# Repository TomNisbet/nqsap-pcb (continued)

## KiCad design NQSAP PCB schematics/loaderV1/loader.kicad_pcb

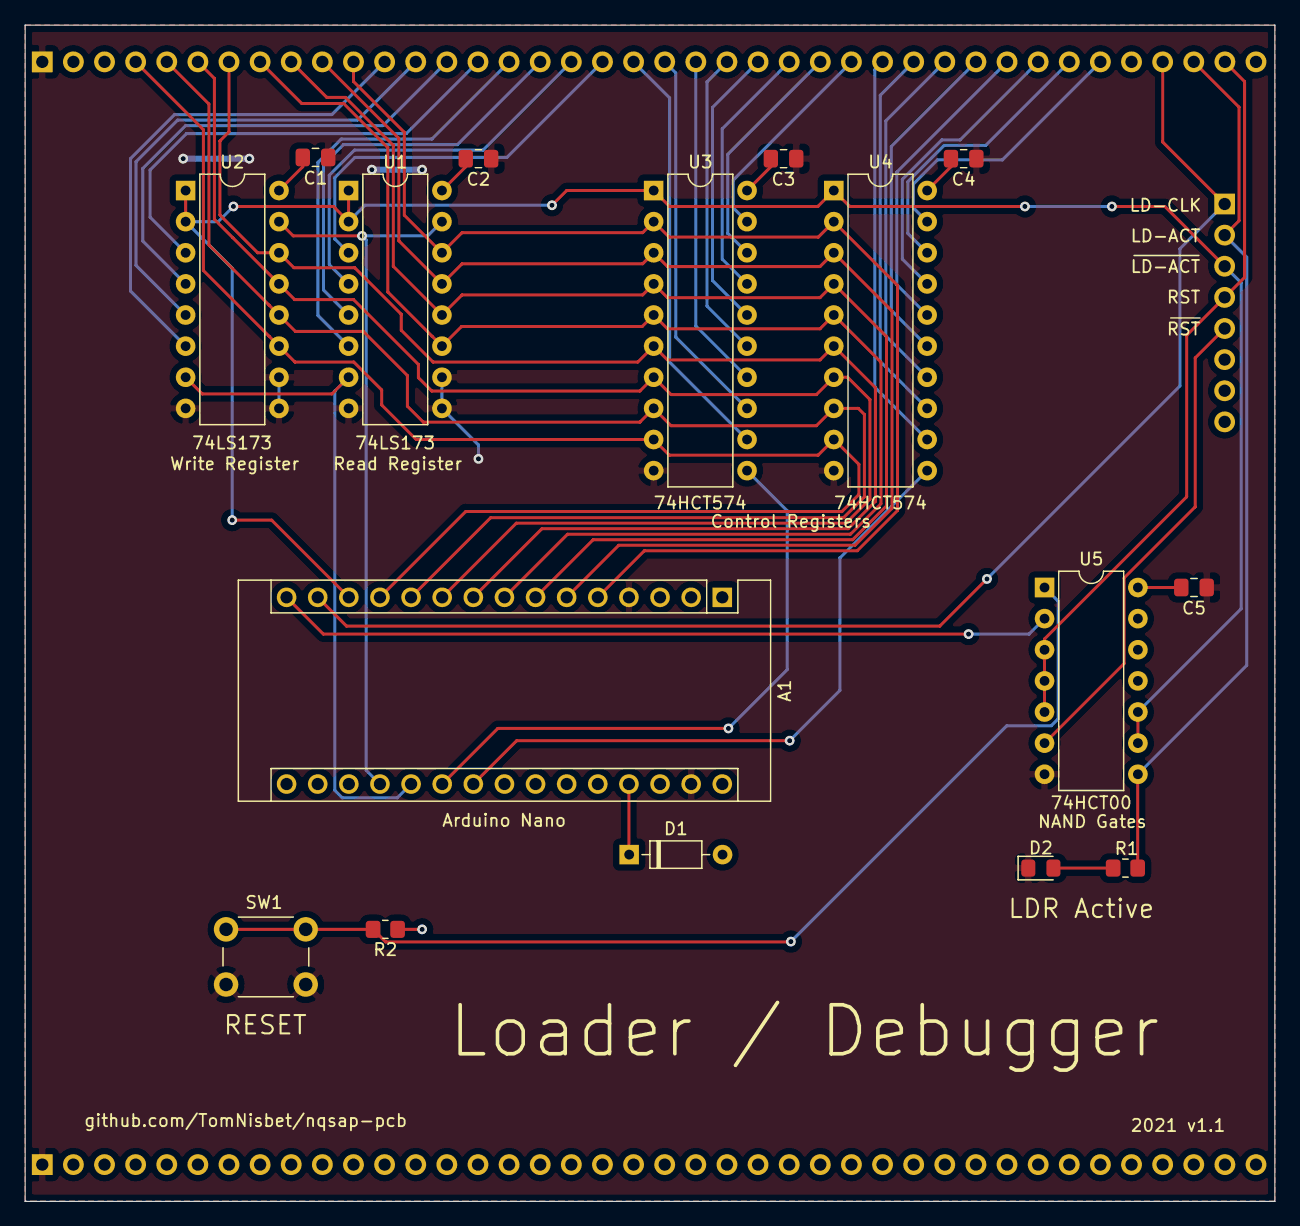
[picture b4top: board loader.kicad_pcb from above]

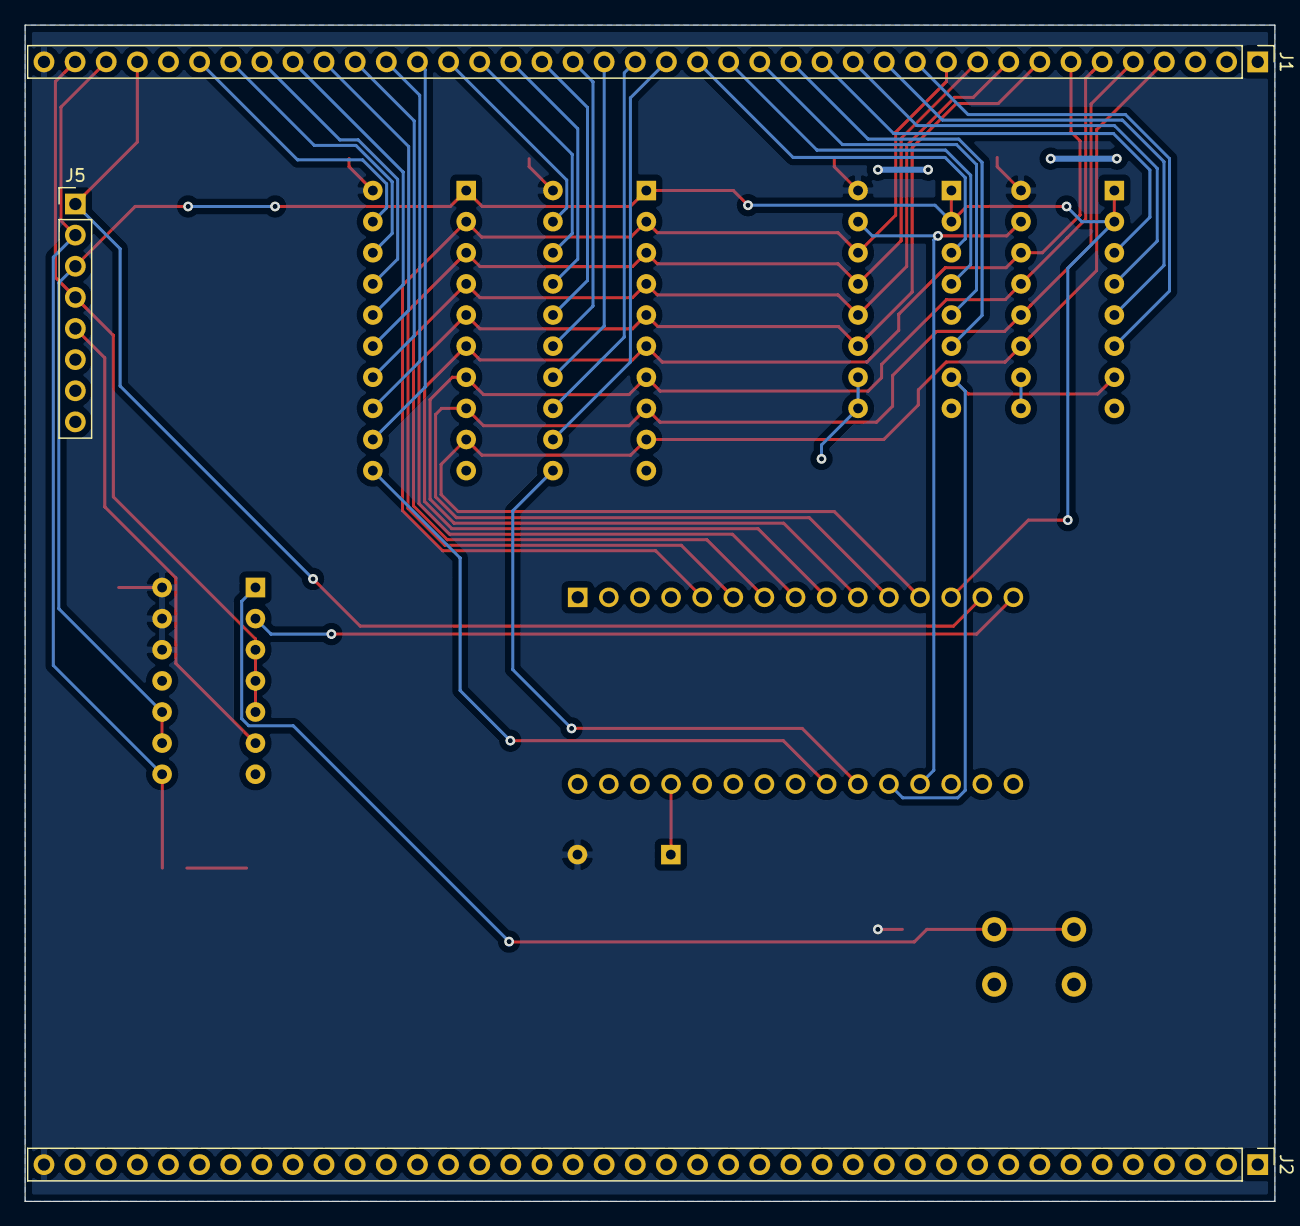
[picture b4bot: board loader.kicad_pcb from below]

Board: 2 copper layers, 102.0 x 96.0 mm, 19 parts (3 on the bottom side), 47 nets.

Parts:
A1: Arduino Nano; Arduino_Nano
C1, C2, C3, C4, C5: 0.1uF; C_0805_2012Metric_Pad1.18x1.45mm_HandSolder
D1: diode; D_DO-35_SOD27_P7.62mm_Horizontal
D2: LDR Active; LED_0805_2012Metric_Pad1.15x1.40mm_HandSolder
J1, J2: Bus; PinHeader_1x40_P2.54mm_Vertical
J5: Conn_02x08; PinHeader_1x08_P2.54mm_Vertical
R1: 100; R_0805_2012Metric_Pad1.20x1.40mm_HandSolder
R2: 10K; R_0805_2012Metric_Pad1.20x1.40mm_HandSolder
SW1: RESET; SW_PUSH_6mm_H7.3mm
U1, U2: 74LS173; DIP-16_W7.62mm
U3, U4: 74HCT574; DIP-20_W7.62mm
U5: 74HCT00; DIP-14_W7.62mm

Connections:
+5V: C1.2, C2.2, C3.2, C4.2, C5.2, D1.2, J1.40, J2.40, R2.1, U1.16, U2.16, U3.20, U4.20, U5.12, U5.13, U5.14
/CLR: A1.19, U1.15, U2.15
/LD0: A1.22, U4.11
/LD1: A1.21, U3.11
/LD2: A1.20, U1.7, U2.7
/~BT-R: R2.2, SW1.2, U5.1
/~LD-R: A1.15, U5.2
C0: J1.27, U3.19
C1: J1.26, U3.18
CC: J1.29, U4.13
CS: J1.28, U4.12
D0: A1.5, J1.11, U1.14, U3.2, U4.2
D1: A1.6, J1.10, U1.13, U3.3, U4.3
D2: A1.7, J1.9, U1.12, U3.4, U4.4
D3: A1.8, J1.8, U1.11, U3.5, U4.5
D4: A1.9, J1.7, U2.14, U3.6, U4.6
D5: A1.10, J1.6, U2.13, U3.7, U4.7
D6: A1.11, J1.5, U2.12, U3.8, U4.8
D7: A1.12, J1.4, U2.11, U3.9, U4.9
FB: J1.24, U3.16
FC: J1.23, U3.15
FN: J1.20, U3.12
FV: J1.21, U3.13
FZ: J1.22, U3.14
GND: A1.4, A1.29, C1.1, C2.1, C3.1, C4.1, C5.1, D2.1, J1.1, J2.1, SW1.1, U1.8, U1.9, U1.10, U2.8, U2.9, U2.10, U3.10, U4.10, U5.7
JE: J1.33, U4.17
LDR-ACT: J1.38, J5.2, R1.1, U5.8
LDR-CLK: A1.14, J1.37, J5.1
LF: J1.32, U4.16
N: J1.34, U4.18
unnamed: A1.27, D1.1
unnamed: D2.2, R1.2
PI: J1.35, U4.19
RR0: J1.19, U1.3
RR1: J1.18, U1.4
RR2: J1.17, U1.5
RR3: J1.16, U1.6
RST: J1.39, J5.4, U5.3, U5.4, U5.5
SE: J1.31, U4.15
SI: J1.30, U4.14
WR0: J1.15, U2.3
WR1: J1.14, U2.4
WR2: J1.13, U2.5
WR3: J1.12, U2.6
XX0: J1.25, U3.17
~LDR-ACT: A1.13, J5.3, U1.1, U1.2, U2.1, U2.2, U3.1, U4.1, U5.9, U5.10
~RST: J5.5, U5.6

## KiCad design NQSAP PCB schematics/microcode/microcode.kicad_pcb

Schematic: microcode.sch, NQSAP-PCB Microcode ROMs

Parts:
C1, C2, C3: 0.1uF; C_0805_2012Metric_Pad1.18x1.45mm_HandSolder
D1: WR3; LED_0805_2012Metric_Pad1.15x1.40mm_HandSolder
D2: WR2; LED_0805_2012Metric_Pad1.15x1.40mm_HandSolder
D3: WR1; LED_0805_2012Metric_Pad1.15x1.40mm_HandSolder
D4: WR0; LED_0805_2012Metric_Pad1.15x1.40mm_HandSolder
D5: RR3; LED_0805_2012Metric_Pad1.15x1.40mm_HandSolder
D6: RR2; LED_0805_2012Metric_Pad1.15x1.40mm_HandSolder
D7: RR1; LED_0805_2012Metric_Pad1.15x1.40mm_HandSolder
D8: RR0; LED_0805_2012Metric_Pad1.15x1.40mm_HandSolder
D9: FN; LED_0805_2012Metric_Pad1.15x1.40mm_HandSolder
D10: FV; LED_0805_2012Metric_Pad1.15x1.40mm_HandSolder
D11: FZ; LED_0805_2012Metric_Pad1.15x1.40mm_HandSolder
D12: FC; LED_0805_2012Metric_Pad1.15x1.40mm_HandSolder
D13: FB; LED_0805_2012Metric_Pad1.15x1.40mm_HandSolder
D14: SE; LED_0805_2012Metric_Pad1.15x1.40mm_HandSolder
D15: C1; LED_0805_2012Metric_Pad1.15x1.40mm_HandSolder
D16: C0; LED_0805_2012Metric_Pad1.15x1.40mm_HandSolder
D17: CS; LED_0805_2012Metric_Pad1.15x1.40mm_HandSolder
D18: CC; LED_0805_2012Metric_Pad1.15x1.40mm_HandSolder
D19: M1; LED_0805_2012Metric_Pad1.15x1.40mm_HandSolder
D20: M0; LED_0805_2012Metric_Pad1.15x1.40mm_HandSolder
D21: LF; LED_0805_2012Metric_Pad1.15x1.40mm_HandSolder
D22: JE; LED_0805_2012Metric_Pad1.15x1.40mm_HandSolder
D23: N; LED_0805_2012Metric_Pad1.15x1.40mm_HandSolder
D24: PI; LED_0805_2012Metric_Pad1.15x1.40mm_HandSolder
J1, J2: Bus; PinHeader_1x40_P2.54mm_Vertical
J3: IC-LT; PinHeader_1x04_P2.54mm_Vertical
J5: IC-RT; PinHeader_1x08_P2.54mm_Vertical
J6: IC-RB; PinHeader_1x08_P2.54mm_Vertical
R1, R2, R3, R4, R22, R24: R_RED; R_0805_2012Metric_Pad1.20x1.40mm_HandSolder
R5, R6, R7, R8: R_GRN; R_0805_2012Metric_Pad1.20x1.40mm_HandSolder
R9, R10, R11, R12, R17, R18: R_BLUE; R_0805_2012Metric_Pad1.20x1.40mm_HandSolder
R13, R15, R16, R19, R20, R21, R23: R_YEL; R_0805_2012Metric_Pad1.20x1.40mm_HandSolder
R14: R_WHT; R_0805_2012Metric_Pad1.20x1.40mm_HandSolder
U1, U2, U3: 28C256; DIP-28_W15.24mm_Socket

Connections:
+5V: C1.2, C2.2, C3.2, J1.40, J2.40, U1.1 (A14), U1.27 (~WE), U1.28 (VCC), U2.26 (A13), U2.27 (~WE), U2.28 (VCC), U3.27 (~WE), U3.28 (VCC)
C0: D16.2 (A), J1.27, J2.27, U2.11 (D0)
C1: D15.2 (A), J1.26, J2.26, U2.12 (D1)
CC: D18.2 (A), J1.29, J2.29, U3.18 (D6)
CLK: J1.36, J5.3
CS: D17.2 (A), J1.28, J2.28, U3.19 (D7)
FB: D13.2 (A), J1.24, J2.24, U2.15 (D3)
FC: D12.2 (A), J1.23, J2.23, U2.16 (D4)
FN: D9.2 (A), J1.20, J2.20, U2.19 (D7)
FV: D10.2 (A), J1.21, J2.21, U2.18 (D6)
FZ: D11.2 (A), J1.22, J2.22, U2.17 (D5)
GND: C1.1, C2.1, C3.1, J1.1, J2.1, R1.2, R2.2, R3.2, R4.2, R5.2, R6.2, R7.2, R8.2, R9.2, R10.2, R11.2, R12.2, R13.2, R14.2, R15.2, R16.2, R17.2, R18.2, R19.2, R20.2, R21.2, R22.2, R23.2, R24.2, U1.2 (A12), U1.14 (GND), U1.20 (~CS), U1.26 (A13), U2.1 (A14), U2.2 (A12), U2.14 (GND), U2.20 (~CS), U3.1 (A14), U3.2 (A12), U3.14 (GND), U3.20 (~CS), U3.26 (A13)
JE: D22.2 (A), J1.33, J2.33, U3.13 (D2)
LD-ACT: J3.4, J5.4, U1.22 (~OE), U2.22 (~OE), U3.22 (~OE)
LF: D21.2 (A), J1.32, J2.32, U3.15 (D3)
M0: D20.2 (A), J1.31, J2.31, U3.16 (D4)
M1: D19.2 (A), J1.30, J2.30, U3.17 (D5)
MA0: J5.5, U1.10 (A0), U2.10 (A0), U3.10 (A0)
MA1: J5.6, U1.9 (A1), U2.9 (A1), U3.9 (A1)
MA2: J5.7, U1.8 (A2), U2.8 (A2), U3.8 (A2)
MA3: J5.8, U1.7 (A3), U2.7 (A3), U3.7 (A3)
MA4: J6.1, U1.6 (A4), U2.6 (A4), U3.6 (A4)
MA5: J6.2, U1.5 (A5), U2.5 (A5), U3.5 (A5)
MA6: J6.3, U1.4 (A6), U2.4 (A6), U3.4 (A6)
MA7: J6.4, U1.3 (A7), U2.3 (A7), U3.3 (A7)
MA8: J6.5, U1.25 (A8), U2.25 (A8), U3.25 (A8)
MA9: J6.6, U1.24 (A9), U2.24 (A9), U3.24 (A9)
MA10: J6.7, U1.21 (A10), U2.21 (A10), U3.21 (A10)
MA11: J6.8, U1.23 (A11), U2.23 (A11), U3.23 (A11)
N: D23.2 (A), J1.34, J2.34, U3.12 (D1)
unnamed: D1.1 (K), R1.1
unnamed: D2.1 (K), R2.1
unnamed: D3.1 (K), R3.1
unnamed: D4.1 (K), R4.1
unnamed: D5.1 (K), R5.1
unnamed: D6.1 (K), R6.1
unnamed: D7.1 (K), R7.1
unnamed: D8.1 (K), R8.1
unnamed: D9.1 (K), R9.1
unnamed: D10.1 (K), R10.1
unnamed: D11.1 (K), R11.1
unnamed: D12.1 (K), R12.1
unnamed: D13.1 (K), R13.1
unnamed: D14.1 (K), R14.1
unnamed: D15.1 (K), R15.1
unnamed: D16.1 (K), R16.1
unnamed: D17.1 (K), R17.1
unnamed: D18.1 (K), R18.1
unnamed: D19.1 (K), R19.1
unnamed: D20.1 (K), R20.1
unnamed: D21.1 (K), R21.1
unnamed: D22.1 (K), R22.1
unnamed: D23.1 (K), R23.1
unnamed: D24.1 (K), R24.1
PI: D24.2 (A), J1.35, J2.35, U3.11 (D0)
RR0: D8.2 (A), J1.19, J2.19, U1.11 (D0)
RR1: D7.2 (A), J1.18, J2.18, U1.12 (D1)
RR2: D6.2 (A), J1.17, J2.17, U1.13 (D2)
RR3: D5.2 (A), J1.16, J2.16, U1.15 (D3)
SE: D14.2 (A), J1.25, J2.25, U2.13 (D2)
WR0: D4.2 (A), J1.15, J2.15, U1.16 (D4)
WR1: D3.2 (A), J1.14, J2.14, U1.17 (D5)
WR2: D2.2 (A), J1.13, J2.13, U1.18 (D6)
WR3: D1.2 (A), J1.12, J2.12, U1.19 (D7)
~CLK: J3.2, J5.2
~RST: J1.39, J5.1

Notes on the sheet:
ROM2
ROM1
ROM0
MICROCODE ROMS

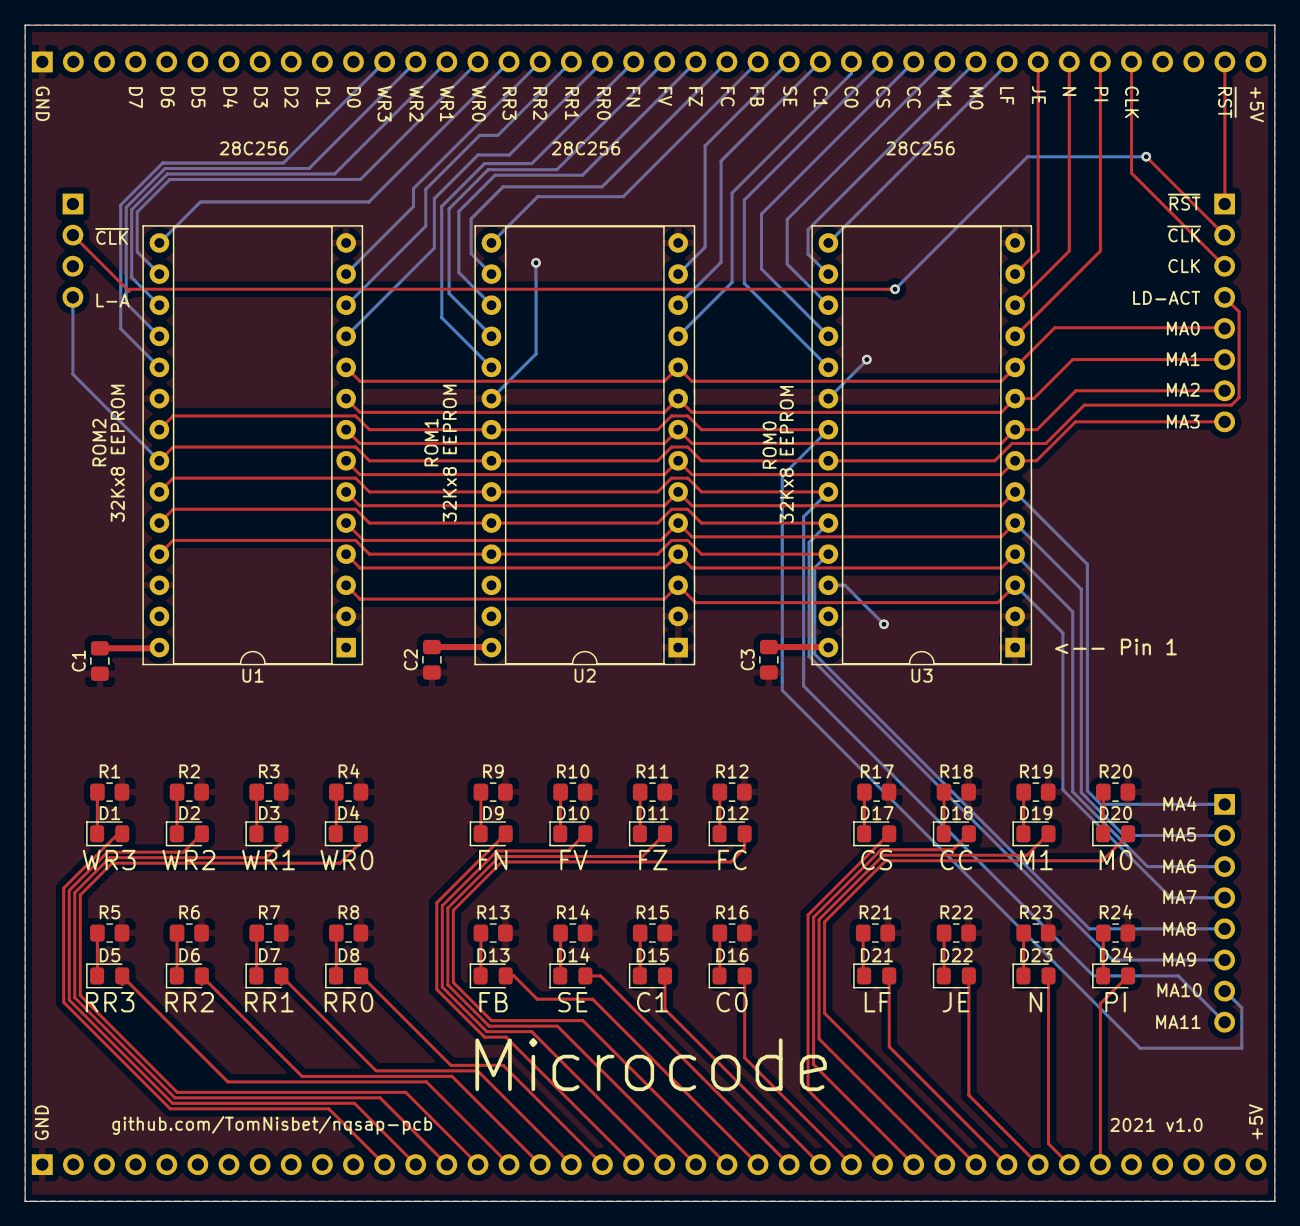
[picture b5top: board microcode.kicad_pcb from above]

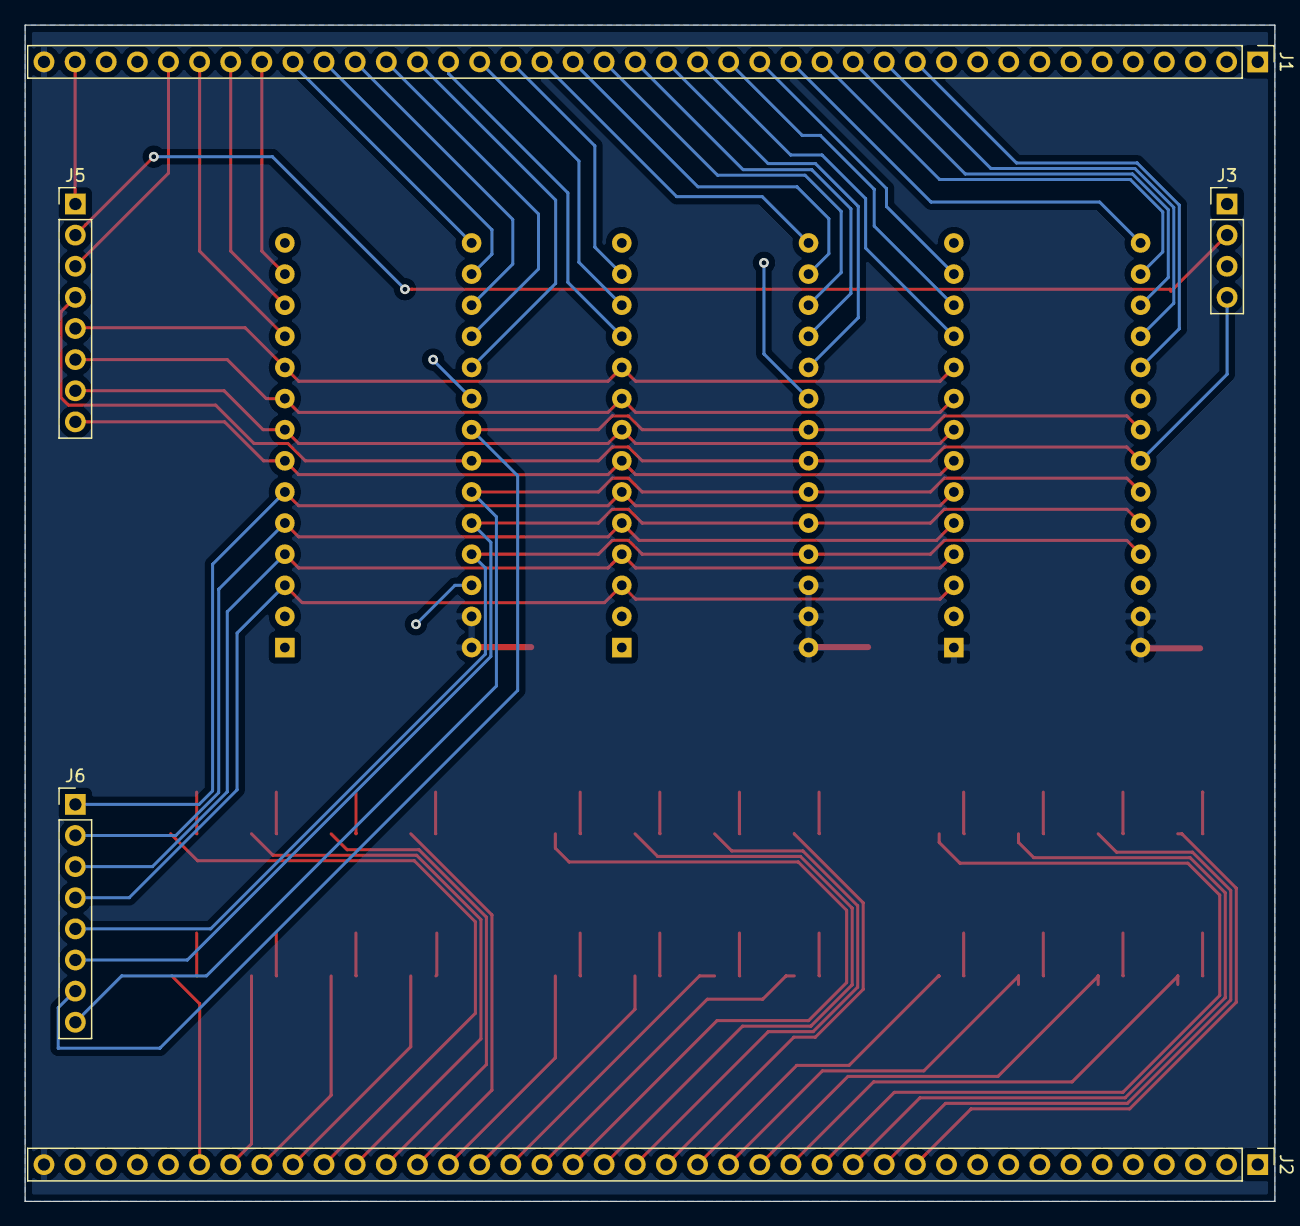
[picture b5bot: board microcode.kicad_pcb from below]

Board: 2 copper layers, 102.0 x 96.0 mm, 59 parts (5 on the bottom side), 66 nets.

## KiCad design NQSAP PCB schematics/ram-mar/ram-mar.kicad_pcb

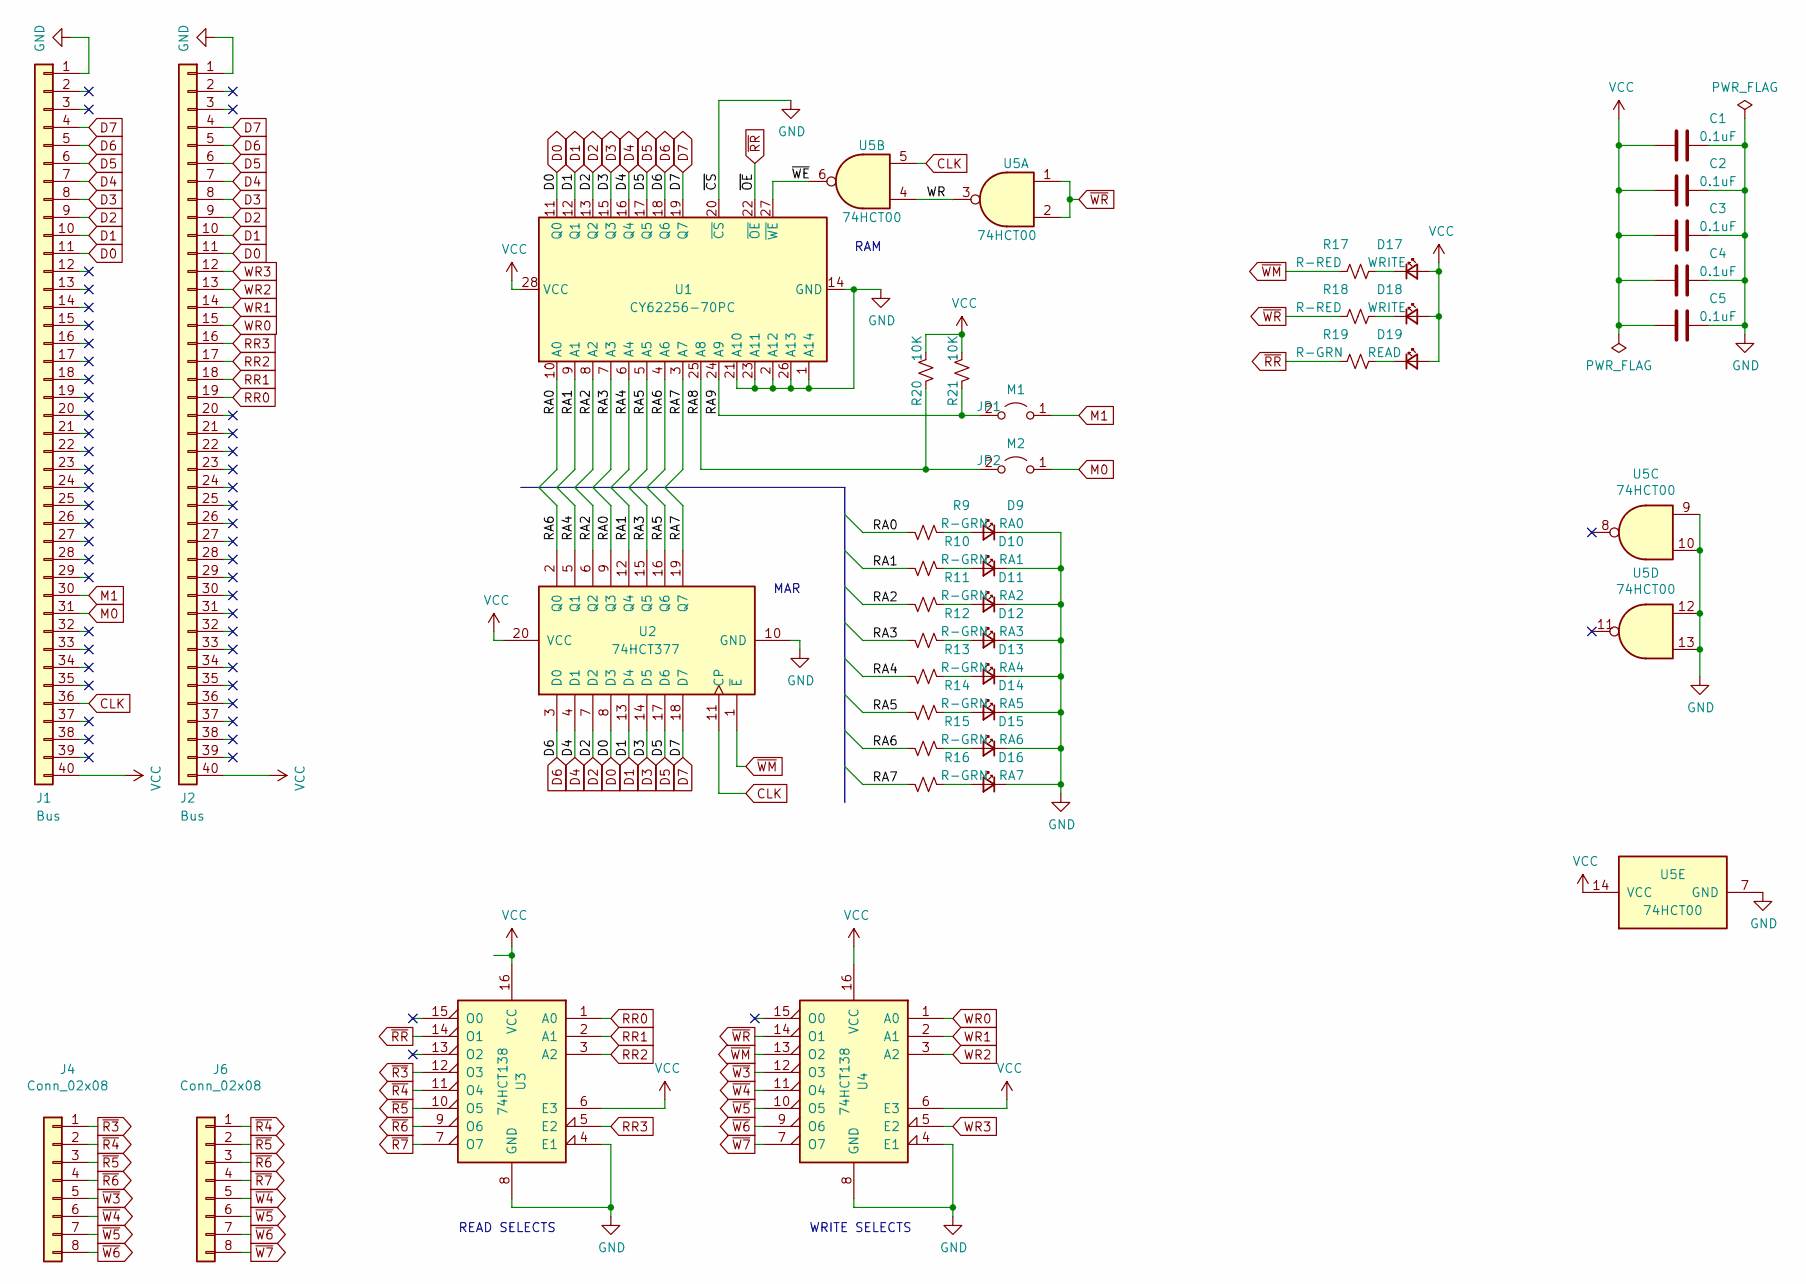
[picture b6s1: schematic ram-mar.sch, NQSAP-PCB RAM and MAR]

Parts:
C1, C2, C3, C4, C5: 0.1uF; C_0805_2012Metric_Pad1.18x1.45mm_HandSolder
D9: RA0; LED_0805_2012Metric_Pad1.15x1.40mm_HandSolder
D10: RA1; LED_0805_2012Metric_Pad1.15x1.40mm_HandSolder
D11: RA2; LED_0805_2012Metric_Pad1.15x1.40mm_HandSolder
D12: RA3; LED_0805_2012Metric_Pad1.15x1.40mm_HandSolder
D13: RA4; LED_0805_2012Metric_Pad1.15x1.40mm_HandSolder
D14: RA5; LED_0805_2012Metric_Pad1.15x1.40mm_HandSolder
D15: RA6; LED_0805_2012Metric_Pad1.15x1.40mm_HandSolder
D16: RA7; LED_0805_2012Metric_Pad1.15x1.40mm_HandSolder
D17, D18: WRITE; LED_0805_2012Metric_Pad1.15x1.40mm_HandSolder
D19: READ; LED_0805_2012Metric_Pad1.15x1.40mm_HandSolder
J1, J2: Bus; PinHeader_1x40_P2.54mm_Vertical
J4, J6: Conn_02x08; PinHeader_1x08_P2.54mm_Vertical
JP1: M1; PinHeader_1x02_P2.54mm_Vertical
JP2: M2; PinHeader_1x02_P2.54mm_Vertical
R9, R10, R11, R12, R13, R14, R15, R16, R19: R-GRN; R_0805_2012Metric_Pad1.20x1.40mm_HandSolder
R17, R18: R-RED; R_0805_2012Metric_Pad1.20x1.40mm_HandSolder
R20, R21: 10K; R_0805_2012Metric_Pad1.20x1.40mm_HandSolder
U1: CY62256-70PC; DIP-28_W15.24mm_Socket
U2: 74HCT377; DIP-20_W7.62mm
U3, U4: 74HCT138; DIP-16_W7.62mm
U5: 74HCT00; DIP-14_W7.62mm

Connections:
/RA0: R9.1, U1.10 (A0), U2.9 (Q3)
/RA1: R10.1, U1.9 (A1), U2.12 (Q4)
/RA2: R11.1, U1.8 (A2), U2.6 (Q2)
/RA3: R12.1, U1.7 (A3), U2.15 (Q5)
/RA4: R13.1, U1.6 (A4), U2.5 (Q1)
/RA5: R14.1, U1.5 (A5), U2.16 (Q6)
/RA6: R15.1, U1.4 (A6), U2.2 (Q0)
/RA7: R16.1, U1.3 (A7), U2.19 (Q7)
/RA8: JP2.2 (B), R20.1, U1.25 (A8)
/RA9: JP1.2 (B), R21.1, U1.24 (A9)
/WR: U5.3, U5.4
/~WE: U1.27 (~WE), U5.6
CLK: J1.36, U2.11 (CP), U5.5
D0: J1.11, J2.11, U1.11 (Q0), U2.8 (D3)
D1: J1.10, J2.10, U1.12 (Q1), U2.13 (D4)
D2: J1.9, J2.9, U1.13 (Q2), U2.7 (D2)
D3: J1.8, J2.8, U1.15 (Q3), U2.14 (D5)
D4: J1.7, J2.7, U1.16 (Q4), U2.4 (D1)
D5: J1.6, J2.6, U1.17 (Q5), U2.17 (D6)
D6: J1.5, J2.5, U1.18 (Q6), U2.3 (D0)
D7: J1.4, J2.4, U1.19 (Q7), U2.18 (D7)
GND: C1.1, C2.1, C3.1, C4.1, C5.1, D9.1 (K), D10.1 (K), D11.1 (K), D12.1 (K), D13.1 (K), D14.1 (K), D15.1 (K), D16.1 (K), J1.1, J2.1, U1.1 (A14), U1.2 (A12), U1.14 (GND), U1.20 (~CS), U1.21 (A10), U1.23 (A11), U1.26 (A13), U2.10 (GND), U3.4 (E1), U3.8 (GND), U4.4 (E1), U4.8 (GND), U5.7 (GND), U5.9, U5.10, U5.12, U5.13
M0: J1.31, JP2.1 (A)
M1: J1.30, JP1.1 (A)
unnamed: D9.2 (A), R9.2
unnamed: D10.2 (A), R10.2
unnamed: D11.2 (A), R11.2
unnamed: D12.2 (A), R12.2
unnamed: D13.2 (A), R13.2
unnamed: D14.2 (A), R14.2
unnamed: D15.2 (A), R15.2
unnamed: D16.2 (A), R16.2
unnamed: D17.1 (K), R17.1
unnamed: D18.1 (K), R18.1
unnamed: D19.1 (K), R19.1
RR0: J2.19, U3.1 (A0)
RR1: J2.18, U3.2 (A1)
RR2: J2.17, U3.3 (A2)
RR3: J2.16, U3.5 (E2)
VCC: C1.2, C2.2, C3.2, C4.2, C5.2, D17.2 (A), D18.2 (A), D19.2 (A), J1.40, J2.40, R20.2, R21.2, U1.28 (VCC), U2.20 (VCC), U3.6 (E3), U3.16 (VCC), U4.6 (E3), U4.16 (VCC), U5.14 (VCC)
WR0: J2.15, U4.1 (A0)
WR1: J2.14, U4.2 (A1)
WR2: J2.13, U4.3 (A2)
WR3: J2.12, U4.5 (E2)
~R3: J4.1, U3.12 (O3)
~R4: J4.2, J6.1, U3.11 (O4)
~R5: J4.3, J6.2, U3.10 (O5)
~R6: J4.4, J6.3, U3.9 (O6)
~R7: J6.4, U3.7 (O7)
~RR: R19.2, U1.22 (~OE), U3.14 (O1)
~W3: J4.5, U4.12 (O3)
~W4: J4.6, J6.5, U4.11 (O4)
~W5: J4.7, J6.6, U4.10 (O5)
~W6: J4.8, J6.7, U4.9 (O6)
~W7: J6.8, U4.7 (O7)
~WM: R17.2, U2.1 (~E), U4.13 (O2)
~WR: R18.2, U4.14 (O1), U5.1, U5.2

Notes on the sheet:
MAR
RAM
READ SELECTS
WRITE SELECTS

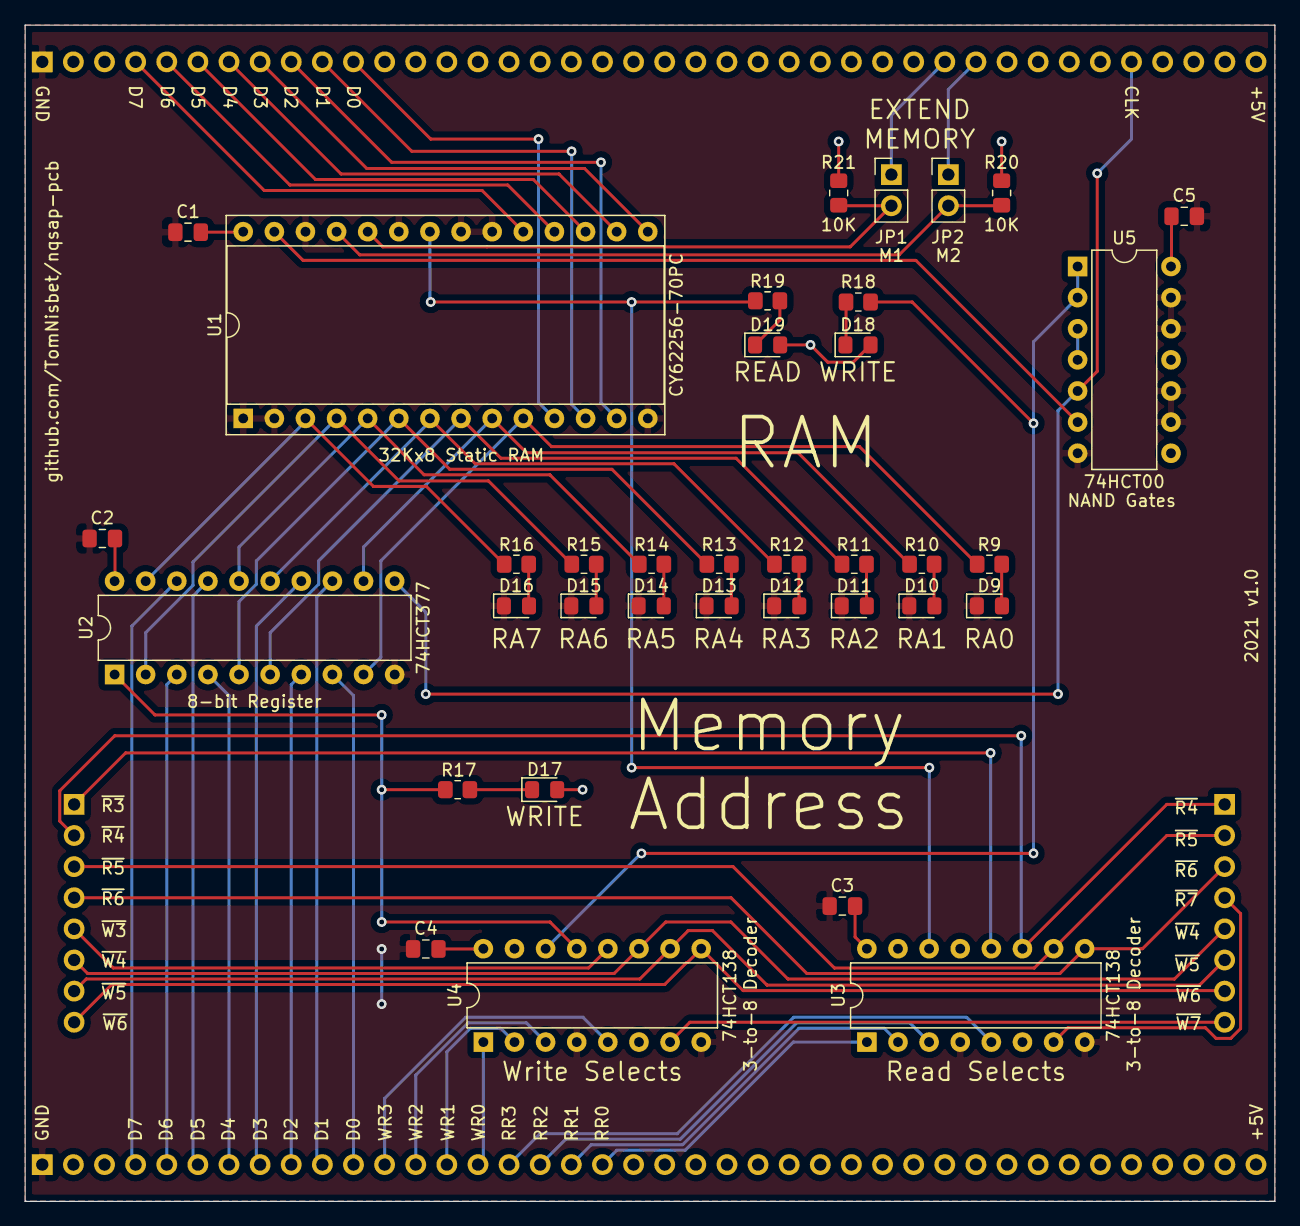
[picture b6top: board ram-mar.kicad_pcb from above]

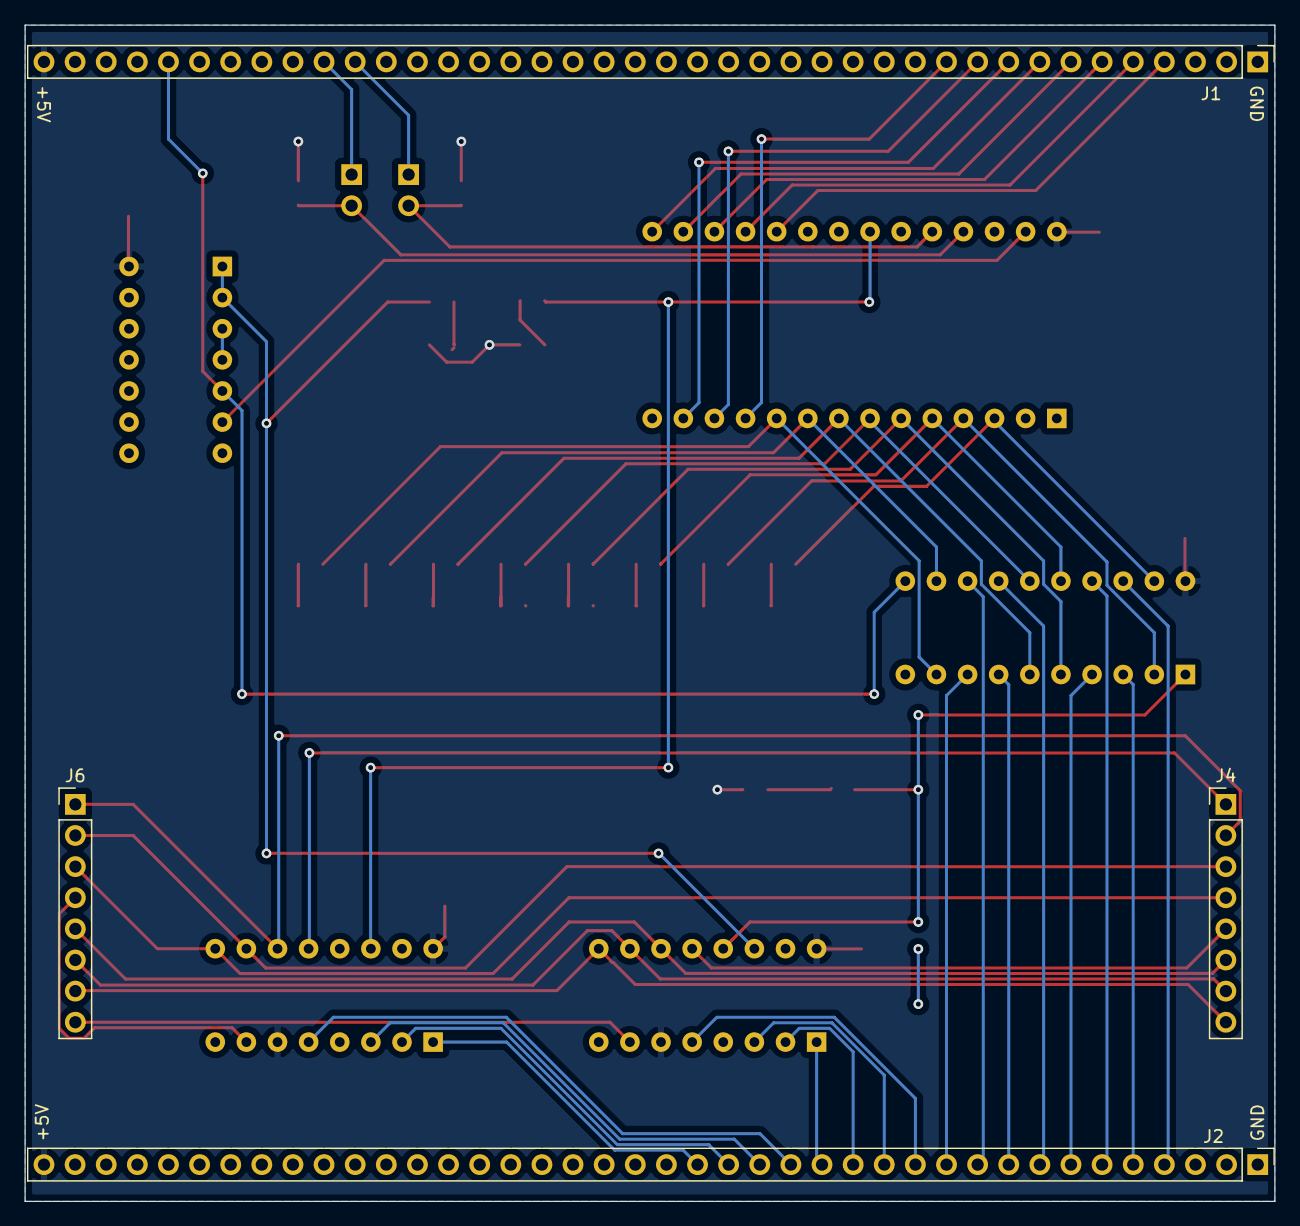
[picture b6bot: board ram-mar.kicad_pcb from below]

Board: 2 copper layers, 102.0 x 96.0 mm, 40 parts (4 on the bottom side), 57 nets.
